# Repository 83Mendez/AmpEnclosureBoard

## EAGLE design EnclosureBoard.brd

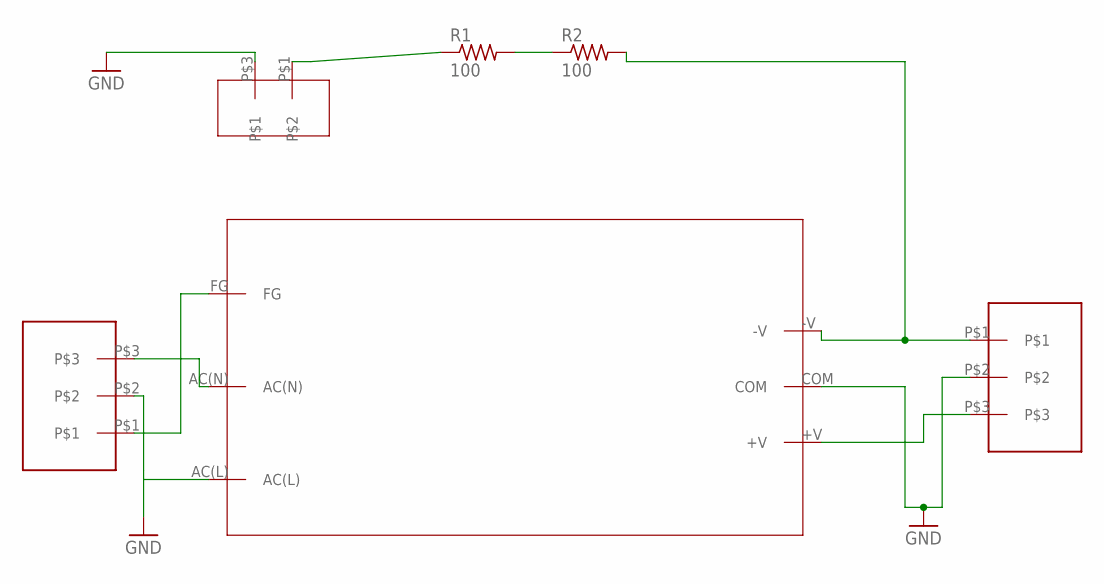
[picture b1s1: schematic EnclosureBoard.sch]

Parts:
R1, R2: 100; 0207/10
U$1: YW1512A-POWER-SUPPLY; YW1512A
U$2, U$3: AC-POWER-ENTRY; 3POSTERMINAL
U$4: 2POSTBLOCK; 2POSTTERMINALBLOCK

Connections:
GND: U$1.AC(L), U$1.COM, U$2.P$2, U$3.P$2, U$4.P$3
unnamed: R1.1, U$4.P$1
unnamed: R1.2, R2.1
unnamed: U$1.FG, U$2.P$1
unnamed: R2.2, U$1.-V, U$3.P$1
unnamed: U$1.AC(N), U$2.P$3
unnamed: U$1.+V, U$3.P$3

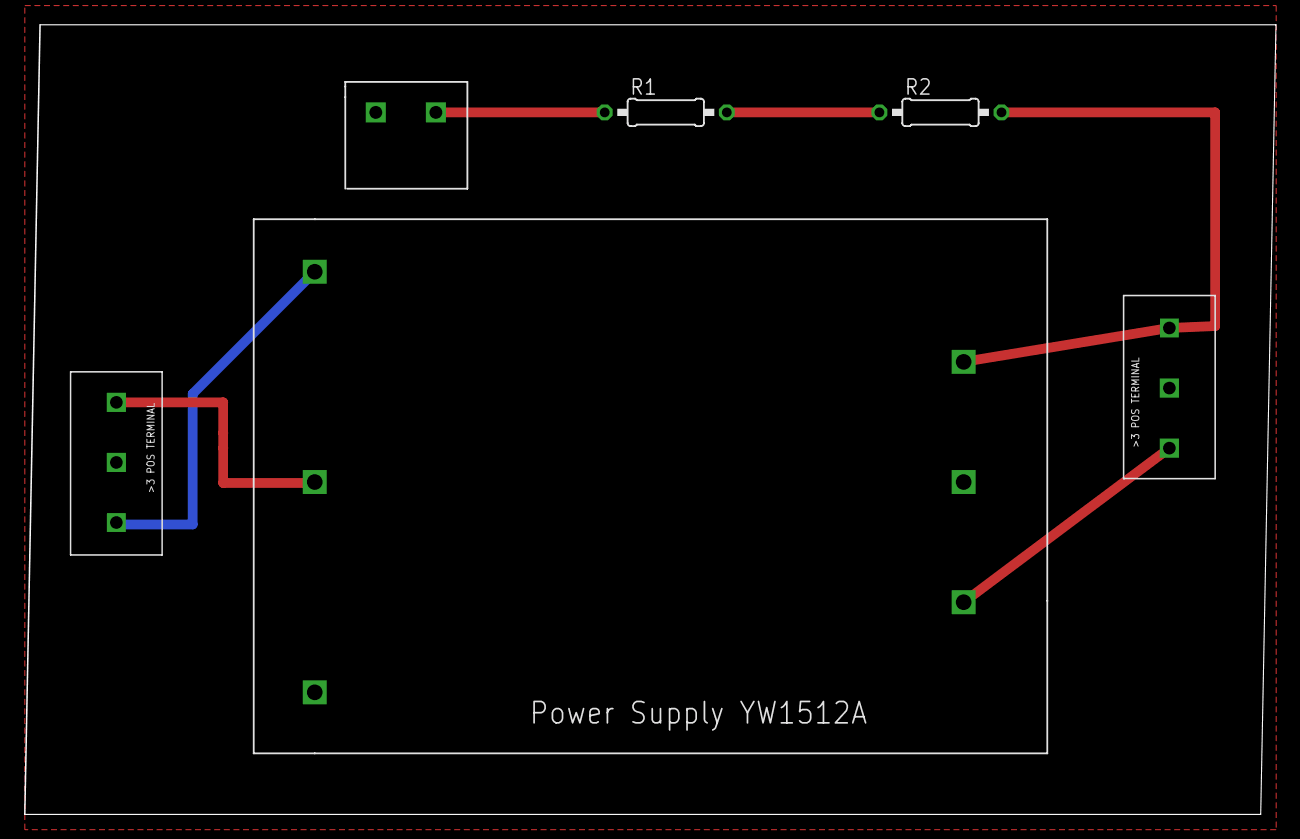
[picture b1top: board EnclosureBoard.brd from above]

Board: 2 copper layers, 104.1 x 65.7 mm, 6 parts (0 on the bottom side), 7 nets.

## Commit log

2019-03-05 Eagle Schematics and Board for AC to DC Amp Enclosure with LED -15 to 15 Volts, 500 mA.
